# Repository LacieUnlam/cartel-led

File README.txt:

Repositorio GIT del LACIE

NOMBRE PROYECTO:
DESCRIPCION CORTA:
URL WIKI:

Estructura de directorios sugerida del GIT:

* kicad: Archivos PCBs del kicad. 
 ** prototipo1: Colocar gerbers, BOM, pdfs del circuito fabricado, fotos, renders.
 ** prototipo2: Si se hace una segunda fabricación  con correcciones.
 ** hojas_datos: Hojas de datos de los componentes usados en el diseño.
 ** lib: bibliotecas del esquemático.
 ** footp: Módulos del PCB. Unificar los módulos en un único archivo.
    *** 3d: Vistas 3D.
* doc: Documentación asociada directamente al desarrolo y al contenido
       del GIT. No repetir la info de la wiki. Se trata de documentación
       generada por el grupo de trabajo o participantes. 
* info: Información relevante y más importante utilizada para el diseño, que
        ayuda a comprenderlo y justificarlo.
        Es información realizada por terceros (si es propia va en doc).
        Notas de aplicación, documentos de terceros, componentes similares
        evaluados, artículos en revistas, etc.

README.txt: Es este archivo, que debe modificarse y actualizarse con los datos   
            del proyecto.

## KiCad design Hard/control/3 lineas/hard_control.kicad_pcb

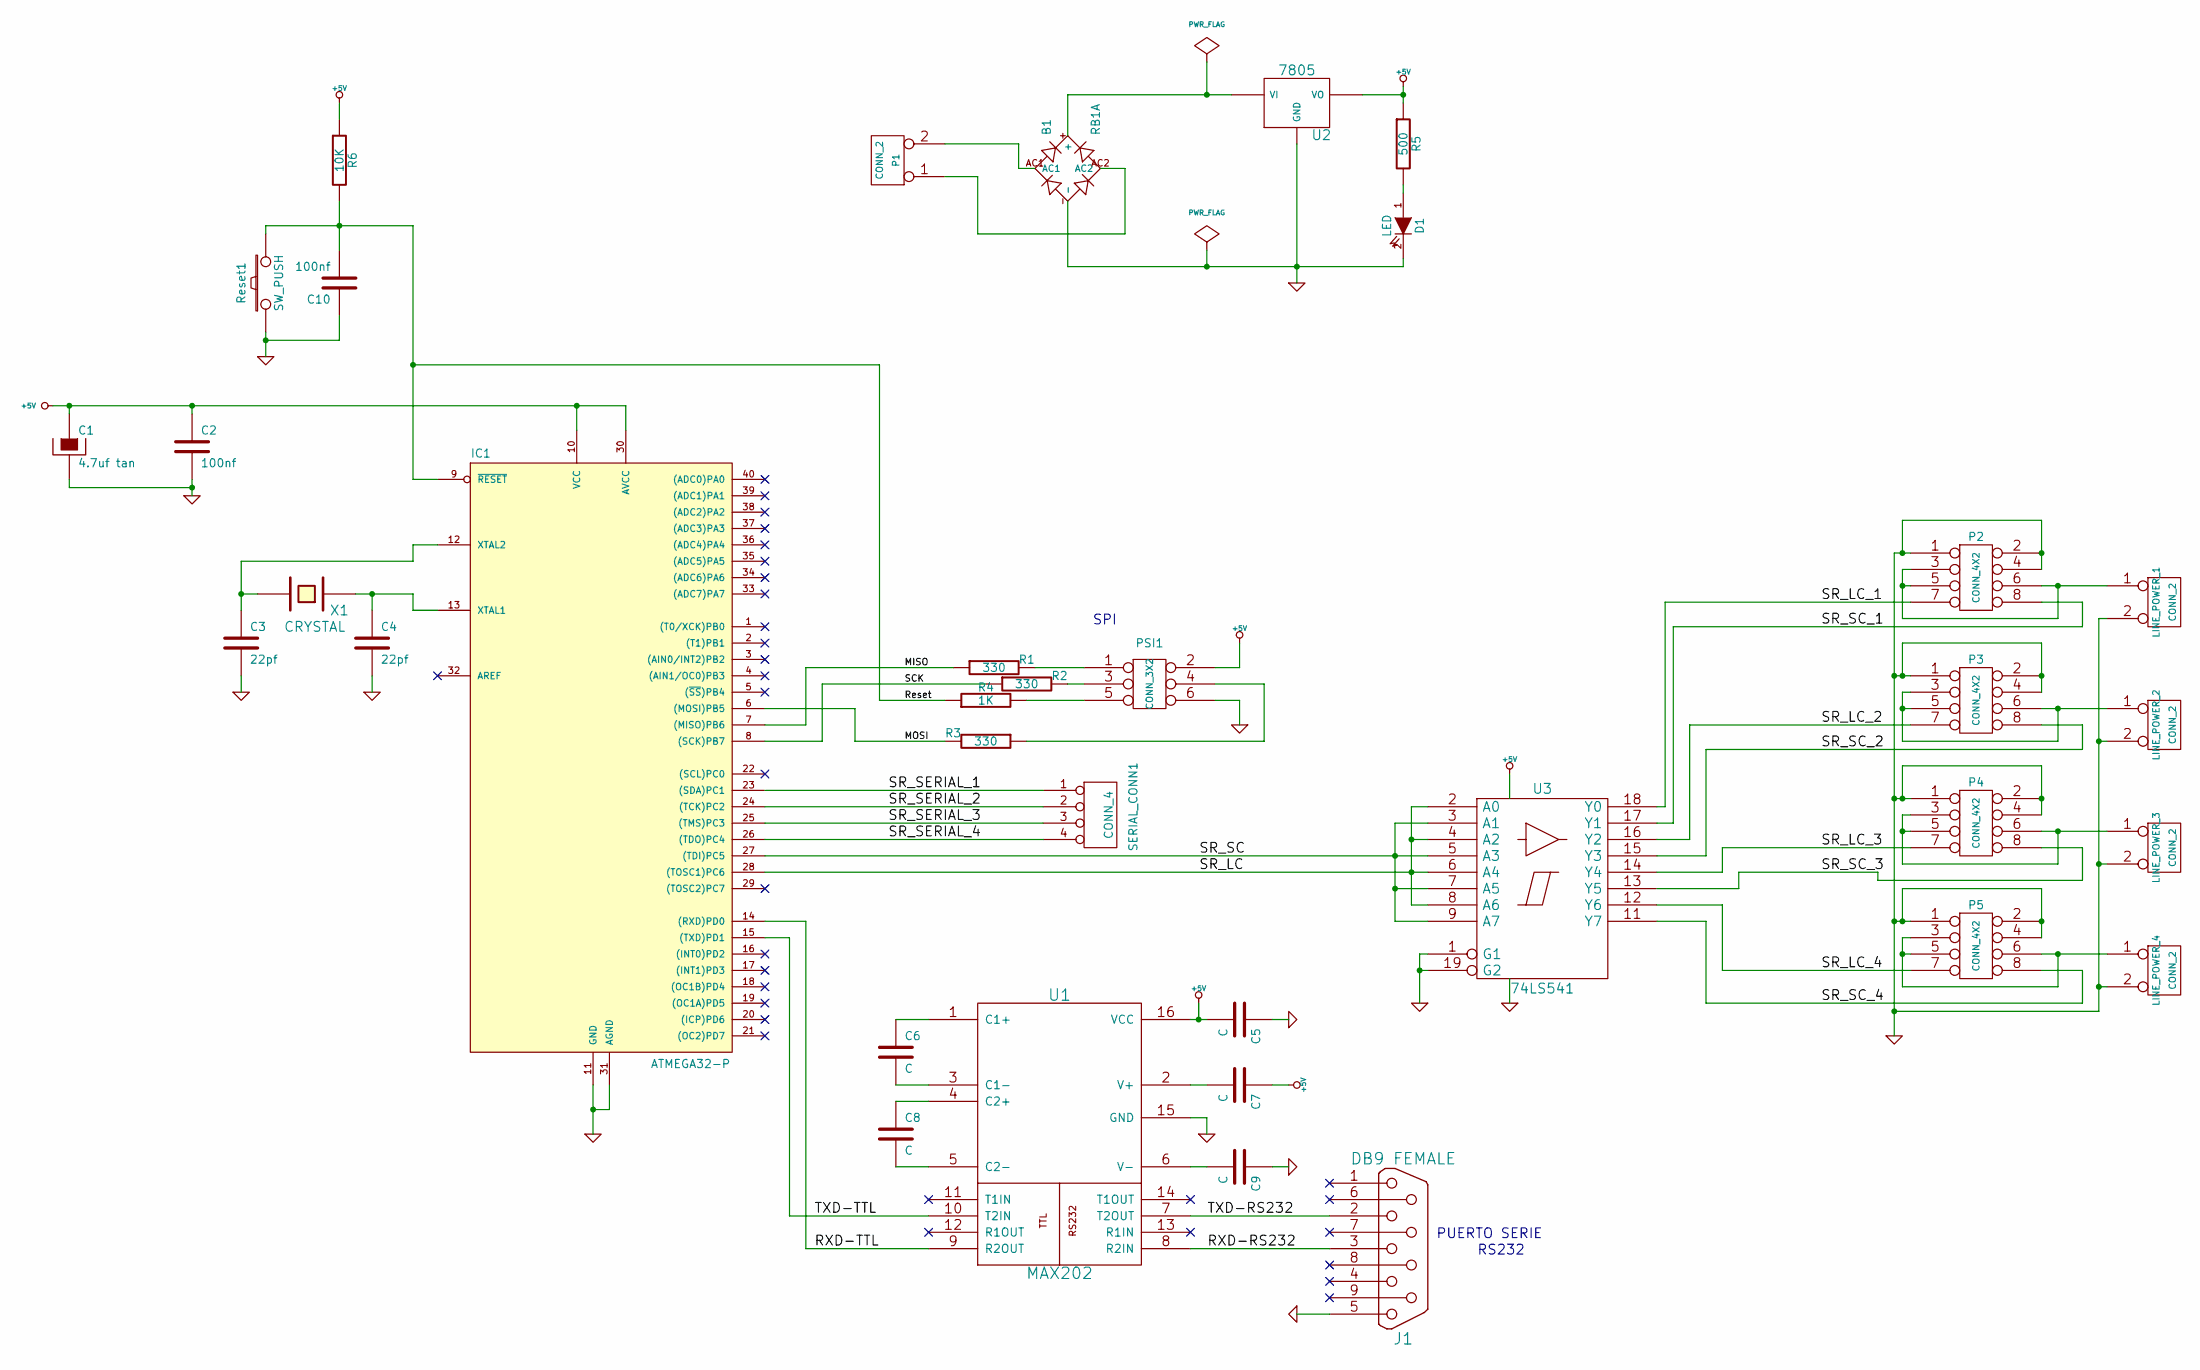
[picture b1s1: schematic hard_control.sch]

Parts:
B1: RB1A; rectifier-RB1A
C1: 4.7uf tan
C2, C10: 100nf
C3, C4: 22pf
C5, C6, C7, C8, C9: C
D1: LED
IC1: ATMEGA32-P; DIL40
J1: DB9 FEMALE
LINE_POWER_1, LINE_POWER_2, LINE_POWER_3, LINE_POWER_4: CONN_2
P1: CONN_2
P2, P3, P4, P5: CONN_4X2
PSI1: CONN_3X2
R1, R2, R3: 330
R4: 1K
R5: 500
R6: 10K
Reset1: SW_PUSH
SERIAL_CONN1: CONN_4
U1: MAX202
U2: 7805
U3: 74LS541
X1: CRYSTAL

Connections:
+5V: C1.1, C2.1, C5.2, C7.1, IC1.10 (VCC), IC1.30 (AVCC), PSI1.2, R5.1, R6.1, U1.16 (VCC), U2.VO, U3.20 (VCC)
/MISO: IC1.7 ((MISO)PB6), R1.1
/MOSI: IC1.6 ((MOSI)PB5), R3.2
/RXD-RS232: J1.3, U1.8 (R2IN)
/RXD-TTL: IC1.14 ((RXD)PD0), U1.9 (R2OUT)
/Reset: C10.2, IC1.9 (~RESET), R4.1, R6.2, Reset1.2
/SCK: IC1.8 ((SCK)PB7), R2.1
/SR_LC: IC1.28 ((TOSC1)PC6), U3.2 (A0), U3.4 (A2), U3.6 (A4), U3.8 (A6)
/SR_LC_1: P2.7, U3.18 (Y0)
/SR_LC_2: P3.7, U3.16 (Y2)
/SR_LC_3: P4.7, U3.14 (Y4)
/SR_LC_4: P5.7, U3.12 (Y6)
/SR_SC: IC1.27 ((TDI)PC5), U3.3 (A1), U3.5 (A3), U3.7 (A5), U3.9 (A7)
/SR_SC_1: P2.8, U3.17 (Y1)
/SR_SC_2: P3.8, U3.15 (Y3)
/SR_SC_3: P4.8, U3.13 (Y5)
/SR_SC_4: P5.8, U3.11 (Y7)
/SR_SERIAL_1: IC1.23 ((SDA)PC1), SERIAL_CONN1.1
/SR_SERIAL_2: IC1.24 ((TCK)PC2), SERIAL_CONN1.2
/SR_SERIAL_3: IC1.25 ((TMS)PC3), SERIAL_CONN1.3
/SR_SERIAL_4: IC1.26 ((TDO)PC4), SERIAL_CONN1.4
/TXD-RS232: J1.2, U1.7 (T2OUT)
/TXD-TTL: IC1.15 ((TXD)PD1), U1.10 (T2IN)
GND: B1.-, C1.2, C2.2, C3.2, C4.2, C5.1, C9.1, C10.1, D1.2 (K), IC1.11 (GND), IC1.31 (AGND), J1.5, LINE_POWER_1.2 (PM), LINE_POWER_2.2 (PM), LINE_POWER_3.2 (PM), LINE_POWER_4.2 (PM), P2.1, P2.2, P2.4, P3.1, P3.2, P3.4, P4.1, P4.2, P4.4, P5.1, P5.2, P5.4, PSI1.6, Reset1.1, U1.15 (GND), U2.GND, U3.1 (G1), U3.10 (GND), U3.19 (G2)
unnamed: LINE_POWER_3.1, P4.3, P4.5, P4.6
unnamed: LINE_POWER_2.1, P3.3, P3.5, P3.6
unnamed: C3.1, IC1.12 (XTAL2), X1.2
unnamed: LINE_POWER_4.1, P5.3, P5.5, P5.6
unnamed: D1.1 (A), R5.2
unnamed: B1.+, U2.VI
unnamed: B1.AC2, P1.1
unnamed: B1.AC1, P1.2 (PM)
unnamed: PSI1.4, R3.1
unnamed: PSI1.5, R4.2
unnamed: PSI1.3, R2.2
unnamed: PSI1.1, R1.2
unnamed: C4.1, IC1.13 (XTAL1), X1.1
unnamed: C7.2, U1.2 (V+)
unnamed: C8.2, U1.5 (C2-)
unnamed: C8.1, U1.4 (C2+)
unnamed: C6.2, U1.3 (C1-)
unnamed: C6.1, U1.1 (C1+)
unnamed: C9.2, U1.6 (V-)
unnamed: LINE_POWER_1.1, P2.3, P2.5, P2.6

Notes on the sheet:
SPI
PUERTO SERIE
RS232

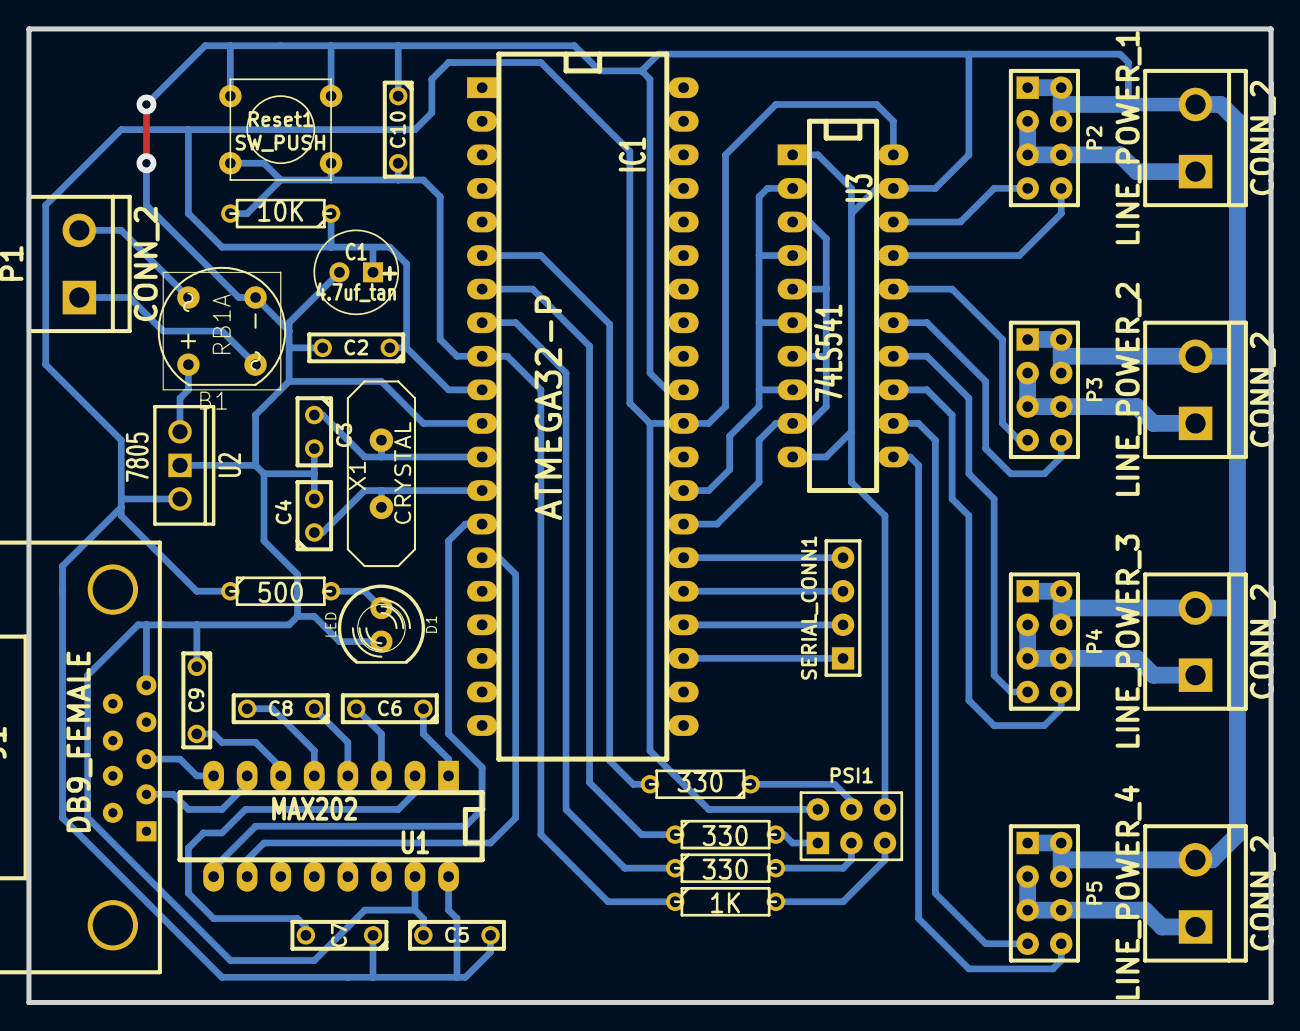
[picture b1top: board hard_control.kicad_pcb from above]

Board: 2 copper layers, 94.0 x 73.7 mm, 36 parts (0 on the bottom side), 44 nets.

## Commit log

2014-05-23 Programa funcionando, especializado para la robolucha. Version robolucha 2013. -Cronometro de round. -Cronometro de tiempo de "actividad incierta" entre contrincantes. -Comando para mostrar dos texto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
2014-05-23 version para testeo placas
2014-05-30 en agregado de comando pausa
2014-05-30 Agregado funcion pausa y eco de contadores por el serial. No ensayado aun.
2014-05-31 pausa y replica de contadores por puerto serial, probados en proteus.
2014-06-10 Terminado,probado:Cronos configurables por trama mm,ss,ccc,s Terminado,probado:Tramas de estado de variables en mm,ss,ccc,s Detectado:Perdida de caracteres en recepción. Detectado:Poco atractiva vist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
2014-10-23 Modificaciones hechas para cartel de 8x6 modulos: *Reposicionado de contadores y nombres de oponentes.
2014-10-27 Agregado: -".gitignore" al versionado -Herramienta GLCDFontCreator al proyecto
2015-05-07 Agregado: -Recursos para control de brillo. Nota: Se perdió la posibilidad de preparar la matriz del cartel en memoria antes de su representación en el cartel, ya que esta matriz esta a su vez trabaj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
    A Resolver:
    -Reponer la capacidad de dibujar por completo la matriz antes de
    actualizar en el cartel.
    Nota: Agregando .gitignore al control de versiones, después de un
    aparentemente fallido intento en commit anterior.
2015-05-11 Agregado el README con instrucciones iniciales.
2015-05-11 Resuelto: -Repuesta la capacidad de dibujar por completo la matriz antes de actualizar en el cartel.
    Nota: Eliminado cartel.c.bak del control de versiones.
2015-05-20 Agrego el PCB del cartel del LEDs y su documentación.
2015-05-21 -Agregado: PCB de placas de control y soft de PC. -Modificado: Reordenamiento de carpetas en el repositorio.
    Nota: Versión commitiada del firm posee modificaciones sin terminar.
2015-05-21 Borro directorio Src con el .bak adentro.
2015-05-21 -Modificado: Eliminado del versionado el descriptor de proyecto Builder (.bpr) de la aplicacion de PC, por poseer direcciones de acceso a librerías que son locales.
2015-06-06 Firm: Inicio rama vent_text. Rama en la que se implementa la representación en el cartel de un fragmento de texto, a nivel de linea de pixeles. Es necesario para una posterior implementación de un sc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
2015-06-08 Terminado: Representación de un fragmento de texto
2015-06-16 Agregado: Implementación de scroll de texto basico.
2015-06-18 Firm: Inicio de agregado de comandos para texto automático
2015-06-27 firm: EnDes: -mensajes en eeprom
2015-06-28 Firm: Terminado: -Comandos de ingreso y representación de mensajes en EEPROM. Modificado: -Asignación de comandos brillo
2015-06-29 Terminado y probado texto en EEPROM y reproducción automática.
2015-07-04 Firm: -Modificado: Presentación de texto EEPROM. Primer linea fija, segunda scroleada.
2015-07-04 Firm: -Modificado: -Presentación de texto EEPROM. Primer linea fija, segunda scroleada. -255 caracteres de texto permitido -La activación de modo "información" detiene contador robolucha si está acti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
2015-10-15 -Adaptada codificación win a utf8 -Inicio de agregado de destello de leds tatami en cuenta regresiva.
2015-10-20 -Primer propuesta de modificaciones para destello de LEDs de tatami, sin probar. -Archivos kicad adaptados a vesion 2015
2015-10-29 -Modificado: los LEDs se mantienen prendidos durante todo el tiempo de operación del cartel, excepto cuando cronometra (se apaga), o cuando se realiza la regresiva (parpadea a cada segundo).
2015-11-02 Agregado soft PC versión robolucha 2015.
2019-09-09 Actualización de los esquemáticos a kicad 5.
2019-09-17 Agrego presentación de la actividad a uea2015.
2026-05-23 Agrego paper uea2015
    Agrego paper presentado al Congreso de Microelectrónica Aplicada 2015.
